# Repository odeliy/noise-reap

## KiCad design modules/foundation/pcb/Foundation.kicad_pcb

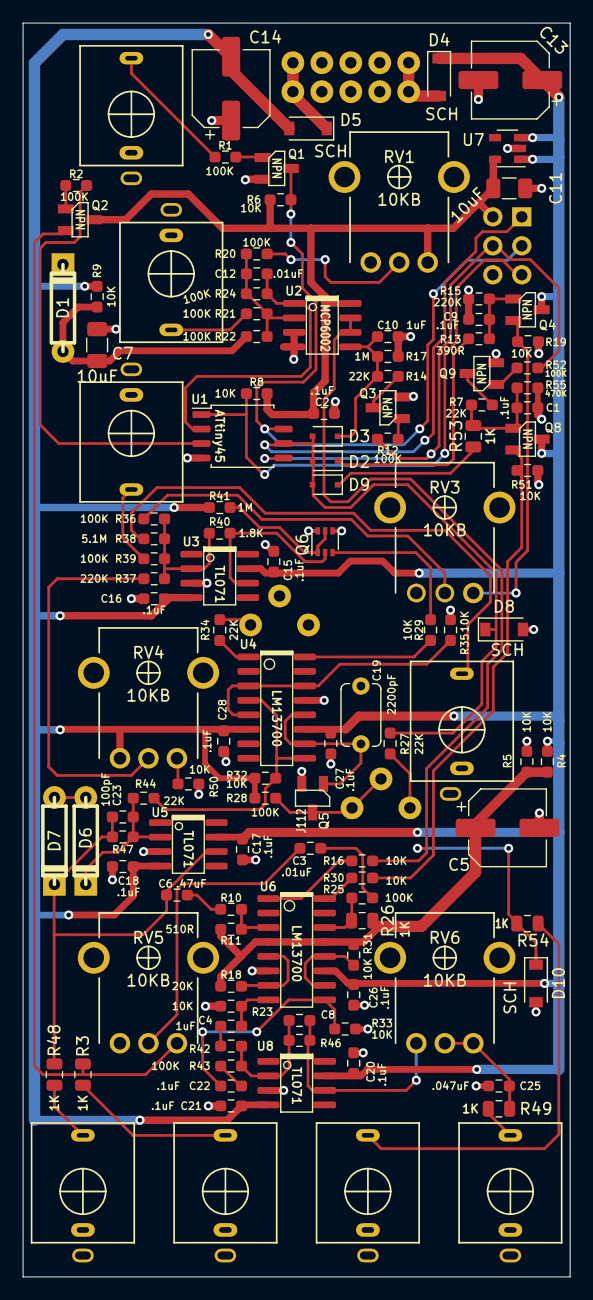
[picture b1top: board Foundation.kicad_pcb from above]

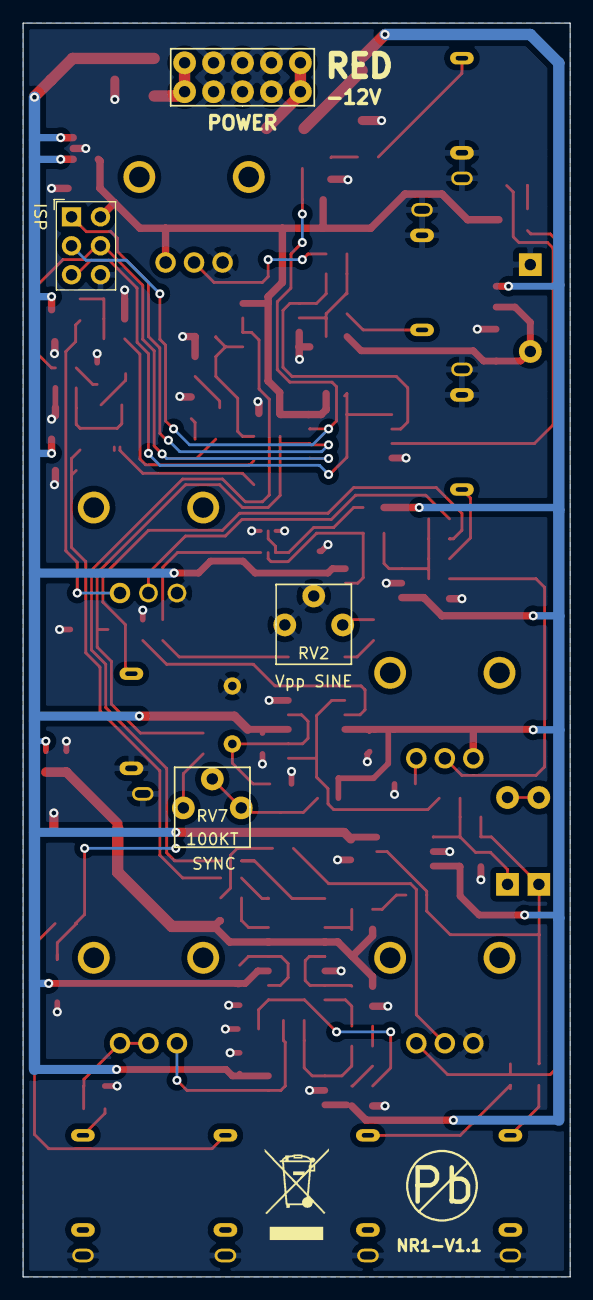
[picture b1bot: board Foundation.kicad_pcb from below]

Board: 2 copper layers, 48.0 x 110.0 mm, 124 parts (4 on the bottom side), 73 nets.

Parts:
C1, C2, C9, C15, C16, C17, C18, C20, C21, C22, C26, C27, C28: .1uF; SM0603
C3, C12: .01uF; SM0603
C4, C10: 1uF; SM0603
C5, C13, C14: 100uF; CP_Elec_6.3x5.4
C6: .47uF; SM0603
C7, C11: 10uF; SM1206
C8, C23: 100pF; SM0603
C19: 2200pF; C_THT_Kemet_Goldmax_C322
C25: .047uF; SM0603
D1, D6, D7: 5.1V; D_THT_DO-41
D2, D3, D9: GEN; D_SOD-323F
D4, D5, D8, D10: SCH; D_SOD-123
J1: STRIKE; AudioJack_QuPing_Pushfit
J2: NOISE; AudioJack_QuPing_Pushfit
J3: AVR-ISP-6; VASCH3x2_ISP
J4: RING_CV; AudioJack_QuPing_Pushfit
J5: POWER; VASCH5x2_unshrouded
J6: NUDGE; AudioJack_QuPing_Pushfit
J7: 1V; AudioJack_QuPing_Pushfit
J8: SINE; AudioJack_QuPing_Pushfit
J9: DRUM; AudioJack_QuPing_Pushfit
J10: ENV_OUT; AudioJack_QuPing_Pushfit
Q1, Q2, Q3, Q4, Q8, Q9: NPN; SOT-23
Q5: J112; SOT-23_nfet
Q6: BC847BPN; SOT-363_SC-70-6
R1, R2, R10, R12, R20, R21, R22, R24, R25, R28, R36, R39, R42, R43, R47, R52: 100K; SM0603
R3, R26, R48, R49, R53, R54: 1K; SM0805
R4, R5, R6, R8, R9, R16, R19, R23, R29, R30, R31, R32, R33, R35, R50, R51: 10K; SM0603
R7, R14, R27, R34, R44: 22K; SM0603
R11: 510R; SM0603
R13: 390R; SM0603
R15, R37, R46: 220K; SM0603
R17, R41: 1M; SM0603
R18: 20K; SM0603
R38: 5.1M; SM0603
R40: 1.8K; SM0603
R55: 470K; SM0603
RV1, RV3, RV4, RV5, RV6: 10KB; POT_9mm_metal
RV2, RV7: 100KT; TRIM_3362P
U1: ATtiny45; SOP-8_5.28x5.23mm_P1.27mm
U2: MCP6002; SOIC-8
U3, U5, U8: TL071; SOIC-8
U4, U6: LM13700; SOIC-16
U7: MIC5205-5.0YM5; SOT-23-5

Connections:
+5V: C2.1, C11.1, J3.2, Q2.C, R6.2, R8.2, RV1.3, U1.8, U2.8, U7.5
+6V: C5.1, R4.2, R5.1, R11.1, R18.2, R26.1, R31.2, U6.4, U6.13
+12V: C13.1, C15.1, C17.1, C20.1, C26.1, C27.1, D4.1, Q4.C, Q8.C, R4.1, U3.7, U4.11, U5.7, U6.11, U7.1, U7.3, U8.7
-5V: C7.1, D1.2, R9.2, R22.2
-12V: C14.2, C16.2, C18.2, C21.2, C28.1, D5.2, R9.1, R28.1, R32.2, R41.2, RV4.1, U3.4, U4.6, U5.4, U8.4
GND: C1.2, C2.2, C5.2, C7.2, C9.2, C10.2, C11.2, C13.2, C14.1, C15.2, C16.1, C17.2, C18.1, C19.2, C20.2, C21.1, C25.2, C26.2, C27.2, C28.2, D1.1, D8.2, D10.2, J1.S, J1.TN, J2.S, J3.6, J4.S, J4.TN, J5.3, J5.4, J5.5, J5.6, J5.7, J5.8, J6.S, J6.TN, J7.S, J7.TN, J8.S, J9.S, J10.S, Q1.E, Q3.E, Q5.S, Q6.4, Q6.6, Q9.E, R5.2, R15.1, R17.2, R19.1, R23.2, R33.2, R35.2, R50.2, R51.2, R55.2, RV1.1, RV2.1, RV2.2, RV3.1, RV5.1, U1.4, U2.3, U2.4, U3.3, U4.13, U5.3, U6.6, U7.2, U8.3
Iexpo: Q6.3, R29.1
unnamed: C1.1, Q8.B, R7.1, R53.1, R55.1
unnamed: C3.1, R25.2
unnamed: C4.2, R23.1, U6.8
unnamed: C6.1, R10.2
unnamed: C8.1, R46.1, RV6.1, U8.6
unnamed: C8.2, R42.1, R43.1, R46.2, U8.2
unnamed: C9.1, Q4.B, R13.1, R15.2
unnamed: C10.1, D3.1, R14.2, R17.1, U2.5
unnamed: C12.2, R20.1, R21.1, R22.1, R24.2, U2.2
unnamed: C19.1, Q5.D, U4.10, U4.12
unnamed: C22.2, R33.1, U6.9
unnamed: C23.2, D6.1, R44.1, R47.2, U5.2
unnamed: C25.1, R49.2, RV6.2, RV6.3
unnamed: D2.1, R13.2
unnamed: D4.2, J5.9, J5.10
unnamed: D5.1, J5.1, J5.2
unnamed: D6.2, D7.2
unnamed: D9.1, R53.2
unnamed: J1.T, R1.2
unnamed: J2.T, R3.1
unnamed: J4.T, R21.2
unnamed: J6.T, R38.2
unnamed: J7.T, R39.2
unnamed: J8.T, R48.1
unnamed: J9.T, R49.1
unnamed: J10.T, R54.1
unnamed: Q1.B, R1.1
unnamed: Q2.B, R2.1
unnamed: Q2.E, R3.2, RV5.3
unnamed: Q3.B, R12.1
unnamed: Q3.C, R14.1
unnamed: Q5.G, R28.2, RV7.2, RV7.3
unnamed: Q6.1, Q6.5, R41.1
unnamed: Q6.2, R40.1, U3.6
unnamed: Q9.B, R52.1
unnamed: Q9.C, R7.2
unnamed: R10.1, R11.2, U6.3
unnamed: R16.2, U6.1
unnamed: R18.1, U6.5, U6.7
unnamed: R20.2, RV1.2
unnamed: R25.1, R26.2, U6.14
unnamed: R27.1, RV7.1
unnamed: R29.2, U4.16
unnamed: R30.2, U6.16
unnamed: R31.1, U6.10, U6.12
unnamed: R34.1, U4.1
unnamed: R34.2, RV2.3
unnamed: R35.1, U4.3, U4.5, U4.14
unnamed: R36.1, R37.1, R38.1, R39.1, R40.2, U3.2
unnamed: R36.2, RV3.2
unnamed: R37.2, RV4.2
unnamed: R50.1, RV4.3
RST: J3.5, R8.1, U1.1
decayPin: C12.1, R24.1, U1.2, U2.1
env1: D10.1, R16.1, R54.2, U2.6, U2.7
env2: Q4.E, R19.2, RV3.3
env3: Q8.E, R30.1, R51.1
noiseDrum: C22.1, R43.2
noisePin: R2.2, U1.3
pulsePin: D2.2, D3.2, D8.1, D9.2, J3.1, R27.2, U1.6
pwmPin: J3.4, R12.2, R52.2, U1.5
sine: C6.2, C23.1, D7.1, R47.1, R48.2, U5.6
sineDrum: C4.1, R42.2
texture: C3.2, RV5.2
triangle: R32.1, R44.2, U4.4, U4.9
trigPin: J3.3, Q1.C, R6.1, U1.7

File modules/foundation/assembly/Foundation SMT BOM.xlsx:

Comment | Designator | Footprint | LCSC Part #
100pF | C8,C23 | C_0603 | C14858
.01uF | C3,C12 | C_0603 | C57112
.047uF | C25 | C_0603 | C1622
.1uF | C28,C27,C26,C9,C1,C15,C2,C16,C17,C18,C20,C21,C22 | C_0603 | C14663
.47uF | C6 | C_0603 | C1623
1uF | C4,C10 | C_0603 | C15849
10uF | C11,C7 | C_1206 | C13585
100uF | C14,C13,C5 | CP_Elec_6.3x5.4 | C134723
390R | R13 | R_0603 | C23151
510R | R11 | R_0603 | C23193
1.8K | R40 | R_0603 | C4177
10K | R33,R19,R51,R50,R30,R4,R5,R6,R8,R9,R16,R23,R29,R31,R32,R35 | R_0603 | C25804
20K | R18 | R_0603 | C4184
22K | R27,R7,R14,R34,R44 | R_0603 | C31850
100K | R52,R2,R1,R10,R12,R20,R21,R22,R24,R25,R28,R36,R39,R42,R43,R47 | R_0603 | C25803
220K | R15,R37,R46 | R_0603 | C22961
470K | R55 | R_0603 | C23178
1M | R17,R41 | R_0603 | C22935
5.1M | R38 | R_0603 | C13320
1K | R54,R53,R48,R26,R3,R49 | R_0805 | C17513
J112 | Q5 | SOT-23-3 | C258195
NPN | Q4,Q9,Q8,Q3,Q2,Q1 | SOT-23-3 | C20526
BC847BPN | Q6 | SOT-363 | C8655
GEN | D9,D3,D2 | D_SOD-323F | C2128
SCH | D10,D8,D5,D4 | D_SOD-123 | C8598
MIC5205-5.0YM5 | U7 | SOT-23-5 | C70431
ATtiny45 | U1 | SOP-8_5.28x5.23mm | C62689
MCP6002 | U2 | SOIC-8 | C7377
TL071 | U5,U8,U3 | SOIC-8 | C107648
LM13700 | U6,U4 | SOIC-16 | C174050

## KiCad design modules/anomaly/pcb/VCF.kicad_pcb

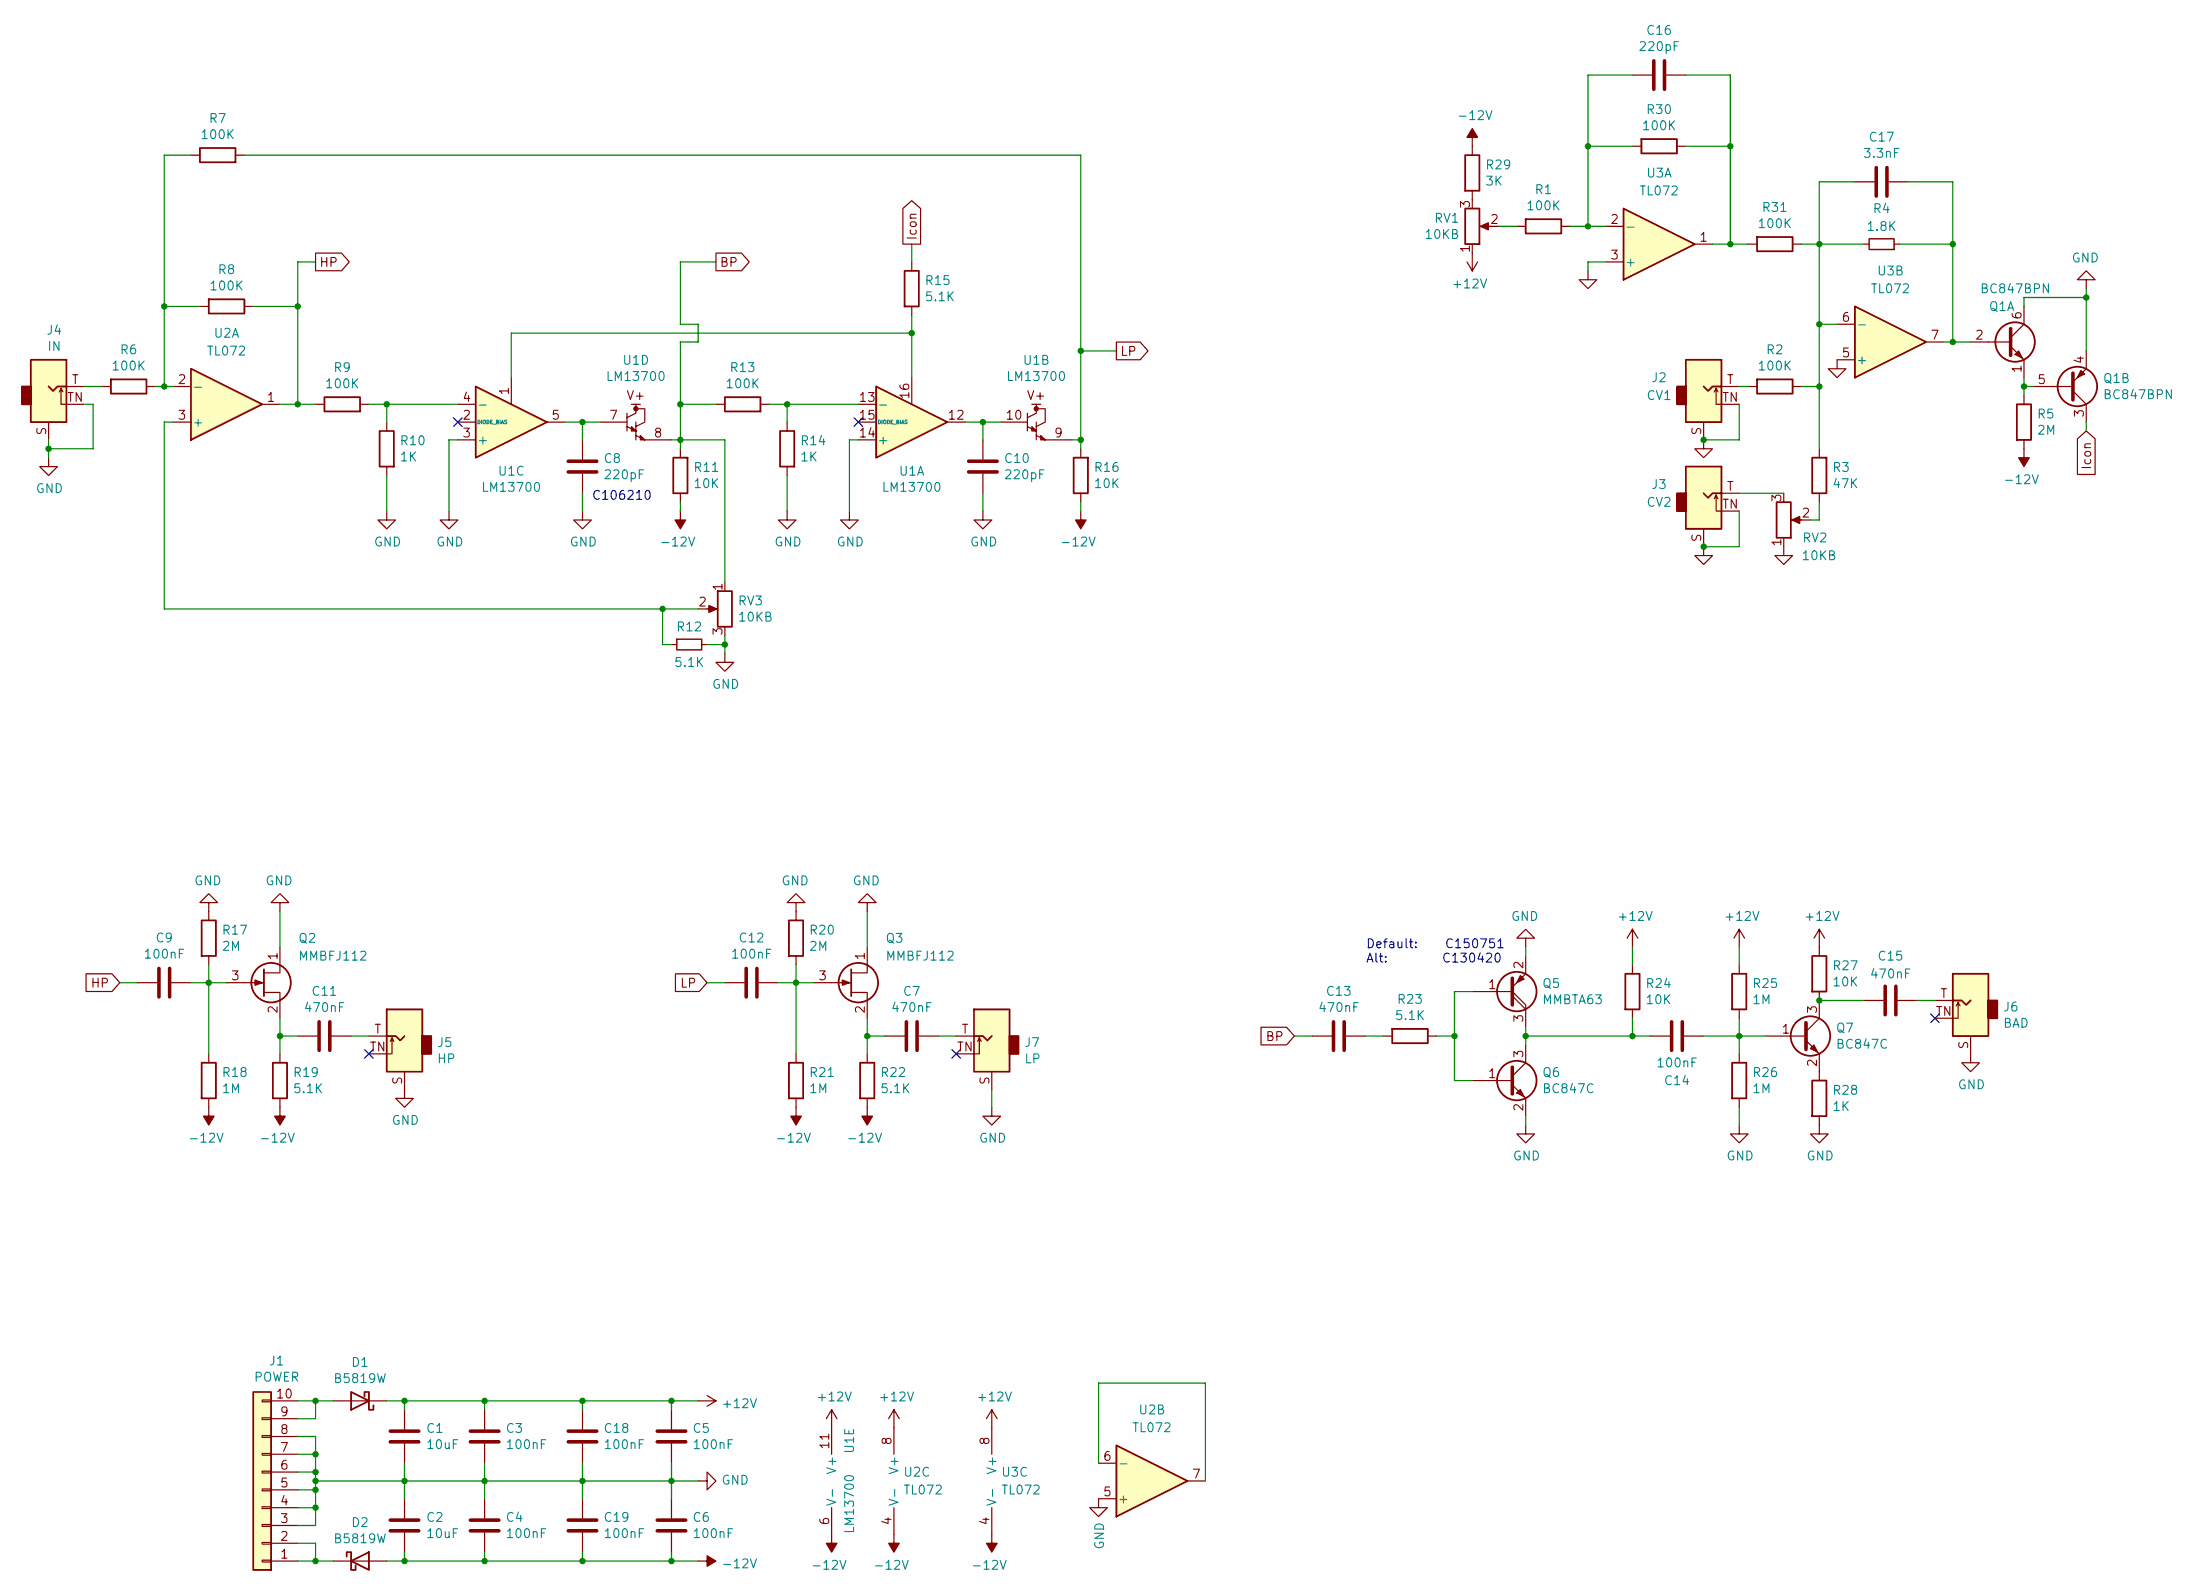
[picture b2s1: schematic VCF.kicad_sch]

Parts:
C1, C2: 10uF; C_1206_3216Metric
C3, C4, C5, C6, C9, C12, C14, C18, C19: 100nF; C_0603_1608Metric
C7, C11, C13, C15: 470nF; C_0805_2012Metric
C8, C10, C16: 220pF; C_0603_1608Metric
C17: 3.3nF; C_0603_1608Metric
D1, D2: B5819W; D_SOD-123
J1: POWER; VASCH5x2_unshrouded
J2: CV1; AudioJack_QuPing_Pushfit
J3: CV2; AudioJack_QuPing_Pushfit
J4: IN; AudioJack_QuPing_Pushfit
J5: HP; AudioJack_QuPing_Pushfit
J6: BAD; AudioJack_QuPing_Pushfit
J7: LP; AudioJack_QuPing_Pushfit
Q1: BC847BPN; SOT-363_SC-70-6
Q2, Q3: MMBFJ112; SOT-23
Q5: MMBTA63; SOT-23
Q6, Q7: BC847C; SOT-23
R1, R2, R6, R7, R8, R9, R13, R30, R31: 100K; R_0603_1608Metric
R3: 47K; R_0603_1608Metric
R4: 1.8K; R_0603_1608Metric
R5, R17, R20: 2M; R_0603_1608Metric
R10, R14, R28: 1K; R_0603_1608Metric
R11, R16, R24, R27: 10K; R_0603_1608Metric
R12, R15, R19, R22, R23: 5.1K; R_0603_1608Metric
R18, R21, R25, R26: 1M; R_0603_1608Metric
R29: 3K; R_0603_1608Metric
RV1, RV2, RV3: 10KB; POT_Bourns_PTV09A-4
U1: LM13700; SOIC-16_3.9x9.9mm_P1.27mm
U2, U3: TL072; SOIC-8_3.9x4.9mm_P1.27mm

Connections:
+12V: C1.1, C3.1, C5.1, C18.1, D1.1 (K), R24.1, R25.1, R27.1, RV1.1, U1.11 (V+), U2.8 (V+), U3.8 (V+)
-12V: C2.2, C4.2, C6.2, C19.2, D2.2 (A), R5.2, R11.1, R16.1, R18.2, R19.2, R21.2, R22.2, R29.1, U1.6 (V-), U2.4 (V-), U3.4 (V-)
BP: C13.2, R11.2, R13.1, RV3.1, U1.8
GND: C1.2, C2.1, C3.2, C4.1, C5.2, C6.1, C8.1, C10.1, C18.2, C19.1, J1.3, J1.4, J1.5, J1.6, J1.7, J1.8, J2.S, J2.TN, J3.S, J3.TN, J4.S, J4.TN, J5.S, J6.S, J7.S, Q1.4 (E2), Q1.6 (C1), Q2.1 (D), Q3.1 (D), Q5.2 (E), Q6.2 (E), R10.2, R12.2, R14.2, R17.1, R20.1, R26.2, R28.2, RV2.1, RV3.3, U1.3 (+), U1.14 (+), U2.5 (+), U3.3 (+), U3.5 (+)
HP: C9.2, R8.1, R9.1, U2.1
Icon: Q1.3 (C2), R15.1
LP: C12.2, R7.2, R16.2, U1.9
unnamed: C7.1, J7.T
unnamed: C7.2, Q3.2 (S), R22.1
unnamed: C8.2, U1.5, U1.7
unnamed: C9.1, Q2.3 (G), R17.2, R18.1
unnamed: C10.2, U1.10, U1.12
unnamed: C11.1, J5.T
unnamed: C11.2, Q2.2 (S), R19.1
unnamed: C12.1, Q3.3 (G), R20.2, R21.1
unnamed: C13.1, R23.2
unnamed: C14.1, Q7.1 (B), R25.2, R26.1
unnamed: C14.2, Q5.3 (C), Q6.3 (C), R24.2
unnamed: C15.1, J6.T
unnamed: C15.2, Q7.3 (C), R27.2
unnamed: C16.1, R30.1, R31.2, U3.1
unnamed: C16.2, R1.1, R30.2, U3.2 (-)
unnamed: C17.1, Q1.2 (B1), R4.1, U3.7
unnamed: C17.2, R2.1, R3.2, R4.2, R31.1, U3.6 (-)
unnamed: D1.2 (A), J1.9, J1.10
unnamed: D2.1 (K), J1.1, J1.2
unnamed: J2.T, R2.2
unnamed: J3.T, RV2.3
unnamed: J4.T, R6.2
unnamed: Q1.1 (E1), Q1.5 (B2), R5.1
unnamed: Q5.1 (B), Q6.1 (B), R23.1
unnamed: Q7.2 (E), R28.1
unnamed: R1.2, RV1.2
unnamed: R3.1, RV2.2
unnamed: R6.1, R7.1, R8.2, U2.2 (-)
unnamed: R9.2, R10.1, U1.4 (-)
unnamed: R12.1, RV3.2, U2.3 (+)
unnamed: R13.2, R14.1, U1.13 (-)
unnamed: R15.2, U1.1, U1.16
unnamed: R29.2, RV1.3
unnamed: U2.6 (-), U2.7

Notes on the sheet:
C106210
Default: C150751 Alt: C130420

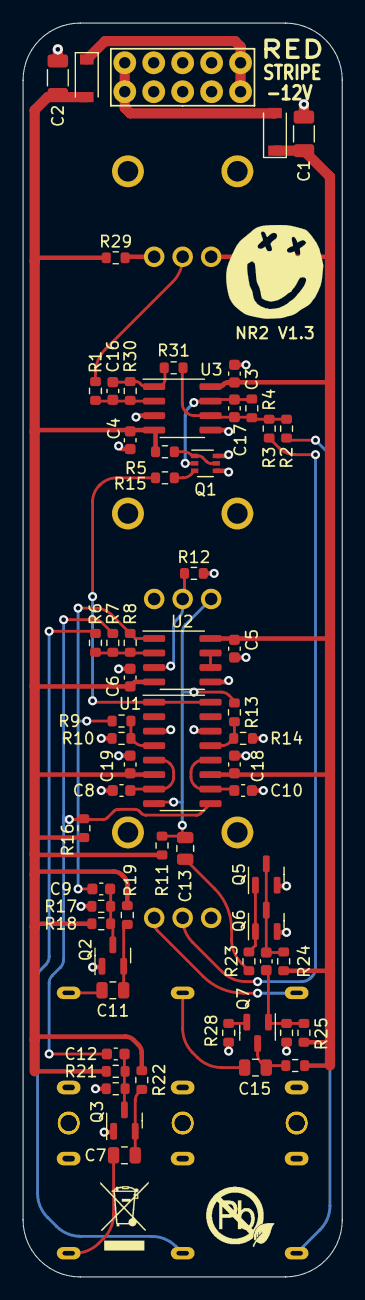
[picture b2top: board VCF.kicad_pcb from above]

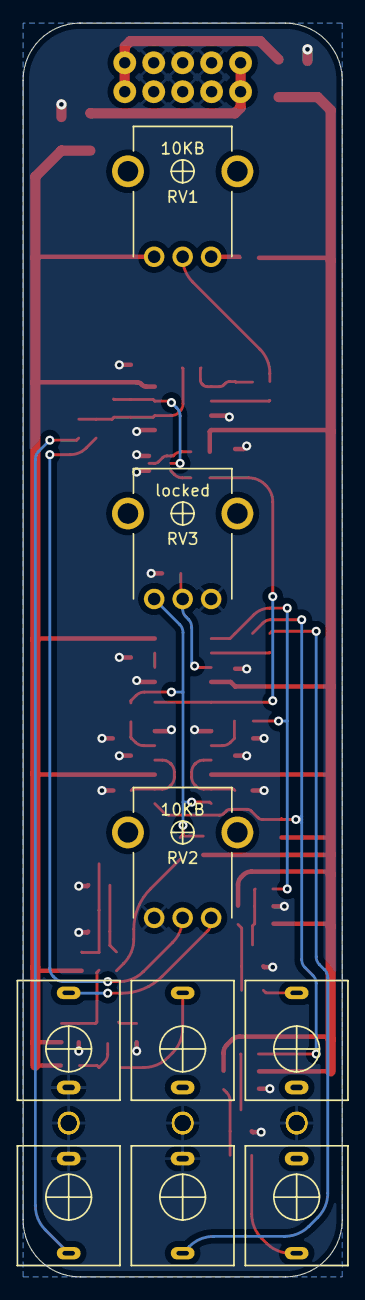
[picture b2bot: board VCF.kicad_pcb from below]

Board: 2 copper layers, 28.0 x 110.0 mm, 72 parts (9 on the bottom side), 41 nets.

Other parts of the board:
U$3: Val**; PB_FREE_EAGLE

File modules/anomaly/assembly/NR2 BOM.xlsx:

Comment | Designator | Footprint | LCSC Part #
220pF NP0 | C16,C10,C8 | C_0603_1608Metric | C106210
3.3nF | C17 | C_0603_1608Metric | C1613
100nF | C14,C3,C12,C9,C6,C4,C19,C18,C5 | C_0603_1608Metric | C14663
470nF | C11,C15,C13,C7 | C_0805_2012Metric | C13967
10uF | C1,C2 | C_1206_3216Metric | C13585
B5819W | D1,D2 | D_SOD-123 | C8598
BC847C | Q6,Q7 | SOT-23 | C181141
MMBTA63-7-F | Q5 | SOT-23 | C130420
MMBFJ112 | Q3,Q2 | SOT-23 | C258195
BC847BPN | Q1 | SOT-363_SC-70-6 | C8655
1K | R10,R14,R28 | R_0603_1608Metric | C21190
1.8K | R4 | R_0603_1608Metric | C4177
3K | R29 | R_0603_1608Metric | C4211
5.1K | R12,R23,R22,R15,R19 | R_0603_1608Metric | C23186
10K | R27,R11,R24,R16 | R_0603_1608Metric | C25804
47K | R3 | R_0603_1608Metric | C25819
100K | R30,R2,R7,R31,R6,R8,R13,R1,R9 | R_0603_1608Metric | C25803
2M | R17,R5,R20 | R_0603_1608Metric | C22976
1M | R25,R18,R21,R26 | R_0603_1608Metric | C22935
LM13700 | U1 | SOIC-16_3.9x9.9mm_P1.27mm | C174050
TL072 | U2,U3 | SOIC-8_3.9x4.9mm_P1.27mm | C6961

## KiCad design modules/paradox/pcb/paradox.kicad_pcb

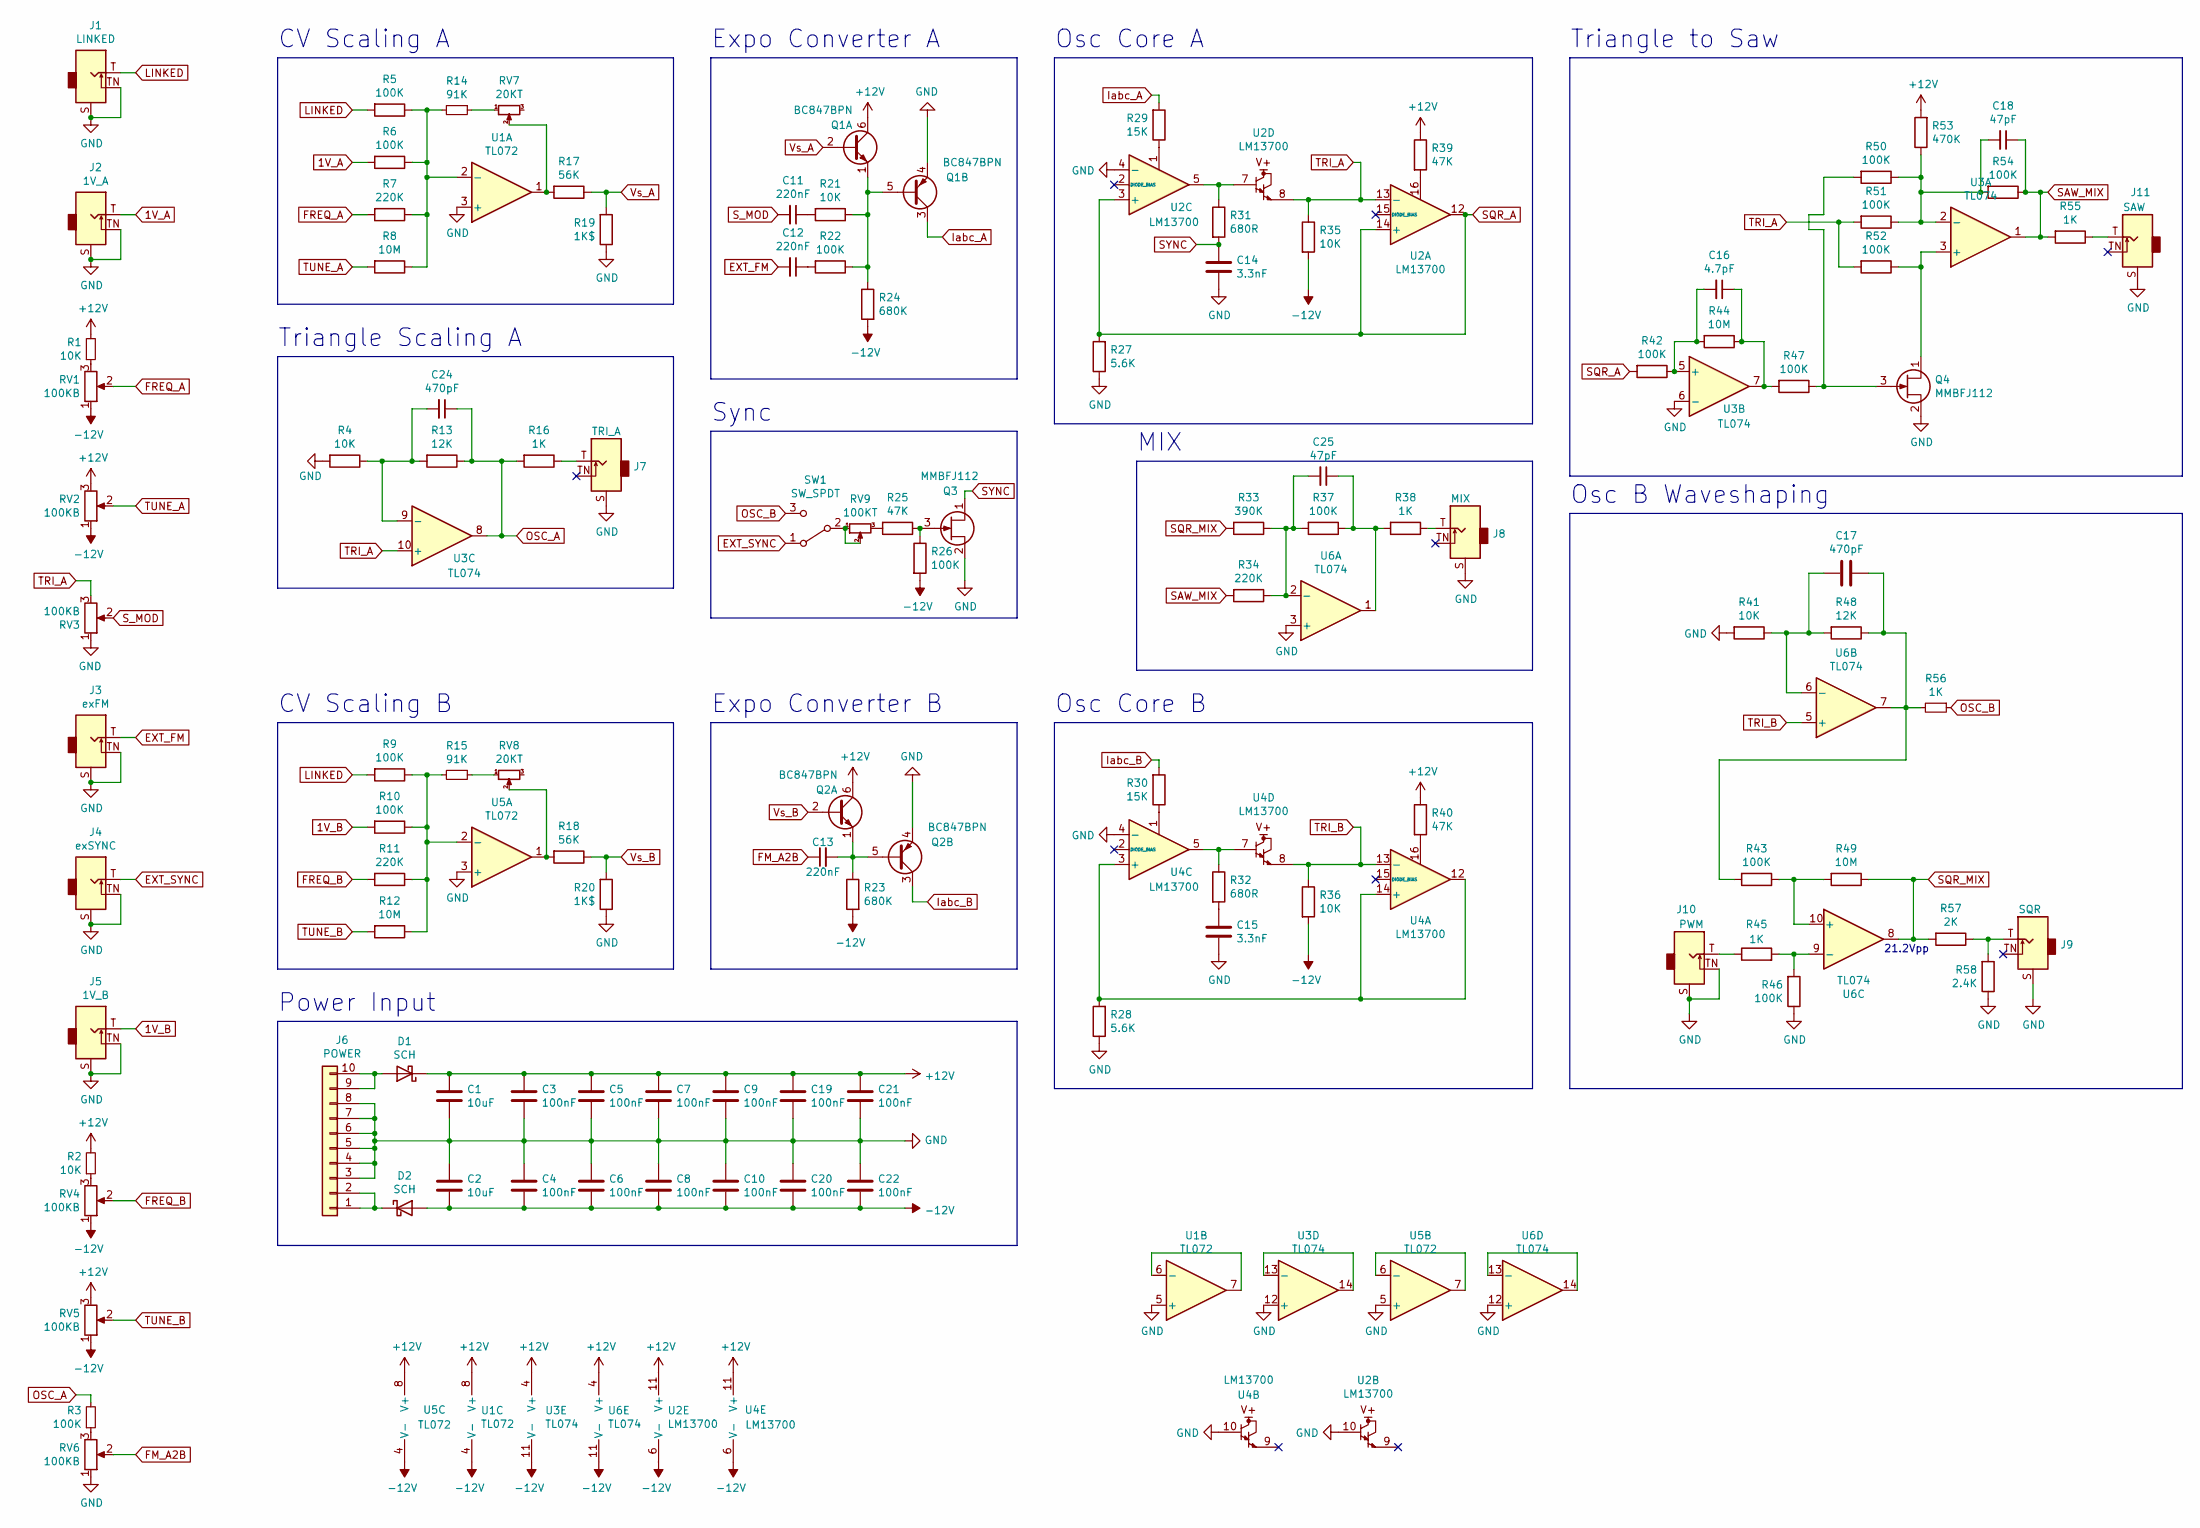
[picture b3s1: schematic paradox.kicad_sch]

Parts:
C1, C2: 10uF; C_1206_3216Metric; JLC C72477
C3, C4, C5, C6, C7, C8, C9, C10, C19, C20, C21, C22: 100nF; C_0402_1005Metric
C11, C12, C13: 220nF; C_0603_1608Metric
C14, C15: 3.3nF; C_0603_1608Metric
C16: 4.7pF; C_0603_1608Metric
C17, C24: 470pF; C_0603_1608Metric
C18, C25: 47pF; C_0603_1608Metric
D1, D2: SCH; D_SOD-123
J1: LINKED; AudioJack_QuPing_Pushfit
J2: 1V_A; AudioJack_QuPing_Pushfit
J3: exFM; AudioJack_QuPing_Pushfit
J4: exSYNC; AudioJack_QuPing_Pushfit
J5: 1V_B; AudioJack_QuPing_Pushfit
J6: POWER; VASCH5x2_unshrouded
J7: TRI_A; AudioJack_QuPing_Pushfit
J8: MIX; AudioJack_QuPing_Pushfit
J9: SQR; AudioJack_QuPing_Pushfit
J10: PWM; AudioJack_QuPing_Pushfit
J11: SAW; AudioJack_QuPing_Pushfit
Q1, Q2: BC847BPN; SOT-363_SC-70-6
Q3, Q4: MMBFJ112; SOT-23
R1, R2, R4, R21, R35, R36, R41: 10K; R_0603_1608Metric
R3, R5, R6, R9, R10, R22, R26, R37, R42, R43, R46, R47, R50, R51, R52, R54: 100K; R_0603_1608Metric
R7, R11, R34: 220K; R_0603_1608Metric
R8, R12, R44, R49: 10M; R_0603_1608Metric
R13, R48: 12K; R_0603_1608Metric
R14, R15: 91K; R_0603_1608Metric
R16, R38, R55: 1K; R_1206_3216Metric
R17, R18: 56K; R_0603_1608Metric
R19, R20: 1K$; R_THT_Tempco
R23, R24: 680K; R_0603_1608Metric
R25, R39, R40: 47K; R_0603_1608Metric
R27, R28: 5.6K; R_0603_1608Metric
R29, R30: 15K; R_0603_1608Metric
R31, R32: 680R; R_0603_1608Metric
R33: 390K; R_0603_1608Metric
R45, R56: 1K; R_0603_1608Metric
R53: 470K; R_0603_1608Metric
R57: 2K; R_0603_1608Metric
R58: 2.4K; R_0603_1608Metric
RV1, RV3, RV4, RV6: 100KB; POT_9mm_P0915N
RV2, RV5: 100KB; POT_9mm_Tall-Trimmer
RV7, RV8: 20KT; TRIM_3296W
RV9: 100KT; TRIM_3296W
SW1: SW_SPDT; SW_SPDT_1M-Series_PC-Thru-Hole
U1, U5: TL072; SOIC-8_3.9x4.9mm_P1.27mm
U2, U4: LM13700; SOIC-16_3.9x9.9mm_P1.27mm
U3, U6: TL074; TSSOP-14_4.4x5mm_P0.65mm

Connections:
1V_A: J2.T, R6.2
1V_B: J5.T, R10.2
+12V: C1.1, C3.1, C5.1, C7.1, C9.1, C19.1, C21.1, D1.1 (K), Q1.6 (C1), Q2.6 (C1), R1.2, R2.2, R39.1, R40.1, R53.2, RV2.3, RV5.3, U1.8 (V+), U2.11 (V+), U3.4 (V+), U4.11 (V+), U5.8 (V+), U6.4 (V+)
-12V: C2.2, C4.2, C6.2, C8.2, C10.2, C20.2, C22.2, D2.2 (A), R23.2, R24.2, R26.2, R35.2, R36.2, RV1.1, RV2.1, RV4.1, RV5.1, U1.4 (V-), U2.6 (V-), U3.11 (V-), U4.6 (V-), U5.4 (V-), U6.11 (V-)
EXT_FM: C12.2, J3.T
EXT_SYNC: J4.T, SW1.1 (A)
FM_A2B: C13.1, RV6.2
FREQ_A: R7.2, RV1.2
FREQ_B: R11.2, RV4.2
GND: C1.2, C2.1, C3.2, C4.1, C5.2, C6.1, C7.2, C8.1, C9.2, C10.1, C14.2, C15.2, C19.2, C20.1, C21.2, C22.1, J1.S, J1.TN, J2.S, J2.TN, J3.S, J3.TN, J4.S, J4.TN, J5.S, J5.TN, J6.3, J6.4, J6.5, J6.6, J6.7, J6.8, J7.S, J8.S, J9.S, J10.S, J10.TN, J11.S, Q1.4 (E2), Q2.4 (E2), Q3.2 (S), Q4.2 (S), R4.2, R19.1, R20.1, R27.1, R28.1, R41.2, R46.1, R58.1, RV3.1, RV6.1, U1.3 (+), U1.5 (+), U2.4 (-), U2.10, U3.6 (-), U3.12 (+), U4.4 (-), U4.10, U5.3 (+), U5.5 (+), U6.3 (+), U6.12 (+)
Iabc_A: Q1.3 (C2), R29.2
Iabc_B: Q2.3 (C2), R30.2
LINKED: J1.T, R5.2, R9.2
unnamed: C11.1, R21.2
unnamed: C12.1, R22.2
unnamed: C13.2, Q2.1 (E1), Q2.5 (B2), R23.1
unnamed: C15.1, R32.2
unnamed: C16.1, R44.1, R47.2, U3.7
unnamed: C16.2, R42.1, R44.2, U3.5 (+)
unnamed: C17.1, R43.2, R48.1, R56.2, U6.7
unnamed: C17.2, R41.1, R48.2, U6.6 (-)
unnamed: C18.2, R50.1, R51.1, R53.1, R54.2, U3.2 (-)
unnamed: C24.2, R4.1, R13.2, U3.9 (-)
unnamed: C25.1, R37.1, R38.2, U6.1
unnamed: C25.2, R33.1, R34.1, R37.2, U6.2 (-)
unnamed: D1.2 (A), J6.9, J6.10
unnamed: D2.1 (K), J6.1, J6.2
unnamed: J7.T, R16.1
unnamed: J8.T, R38.1
unnamed: J9.T, R57.1, R58.2
unnamed: J10.T, R45.1
unnamed: J11.T, R55.1
unnamed: Q1.1 (E1), Q1.5 (B2), R21.1, R22.1, R24.1
unnamed: Q3.3 (G), R25.1, R26.1
unnamed: Q4.1 (D), R52.1, U3.3 (+)
unnamed: Q4.3 (G), R47.1, R50.2
unnamed: R1.1, RV1.3
unnamed: R2.1, RV4.3
unnamed: R3.1, RV6.3
unnamed: R9.1, R10.1, R11.1, R12.1, R15.2, U5.2 (-)
unnamed: R14.1, RV7.1
unnamed: R5.1, R6.1, R7.1, R8.1, R14.2, U1.2 (-)
unnamed: R15.1, RV8.1
unnamed: R17.2, RV7.2, U1.1
unnamed: R18.2, RV8.2, U5.1
unnamed: R25.2, RV9.3
unnamed: R28.2, U4.3 (+), U4.12, U4.14 (+)
unnamed: R29.1, U2.1
unnamed: R30.1, U4.1
unnamed: R31.1, U2.5, U2.7
unnamed: R32.1, U4.5, U4.7
unnamed: R39.2, U2.16
unnamed: R40.2, U4.16
unnamed: R43.1, R49.2, U6.10 (+)
unnamed: R45.2, R46.2, U6.9 (-)
unnamed: RV9.1, RV9.2, SW1.2 (B)
unnamed: U1.6 (-), U1.7
unnamed: U3.13 (-), U3.14
unnamed: U5.6 (-), U5.7
unnamed: U6.13 (-), U6.14
OSC_A: C24.1, R3.2, R13.1, R16.2, U3.8
OSC_B: R56.1, SW1.3 (C)
SAW_MIX: C18.1, R34.2, R54.1, R55.2, U3.1
SQR_A: R27.2, R42.2, U2.3 (+), U2.12, U2.14 (+)
SQR_MIX: R33.2, R49.1, R57.2, U6.8
SYNC: C14.1, Q3.1 (D), R31.2
S_MOD: C11.2, RV3.2
TRI_A: R35.1, R51.2, R52.2, RV3.3, U2.8, U2.13 (-), U3.10 (+)
TRI_B: R36.1, U4.8, U4.13 (-), U6.5 (+)
TUNE_A: R8.2, RV2.2
TUNE_B: R12.2, RV5.2
Vs_A: Q1.2 (B1), R17.1, R19.2
Vs_B: Q2.2 (B1), R18.1, R20.2

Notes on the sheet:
Sync
MIX
21.2Vpp
Expo Converter B
Osc Core A
CV Scaling A
Osc B Waveshaping
Power Input
Osc Core B
Expo Converter A
CV Scaling B
Triangle to Saw
Triangle Scaling A

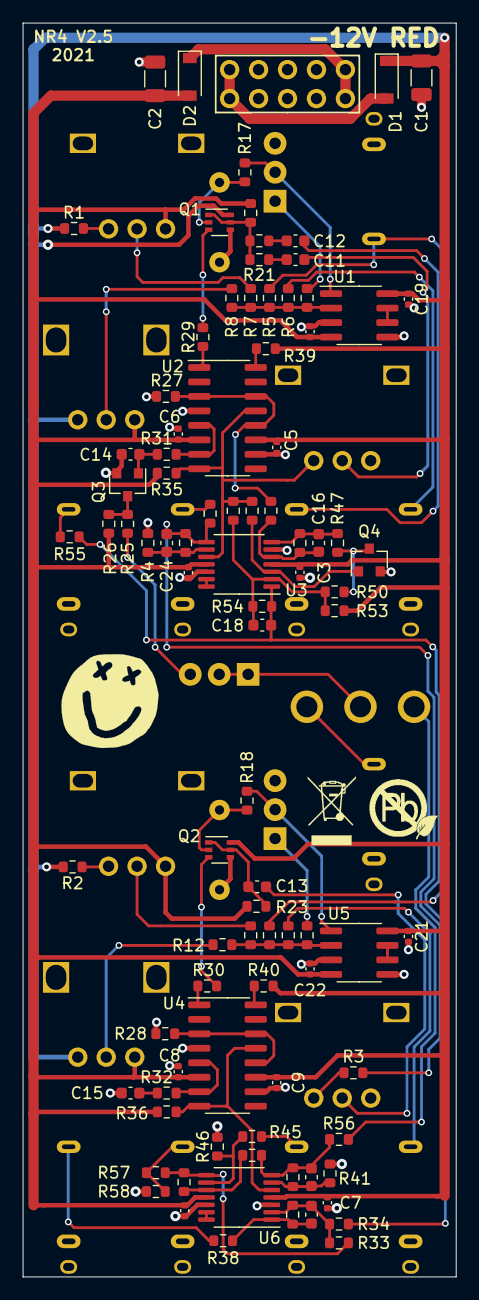
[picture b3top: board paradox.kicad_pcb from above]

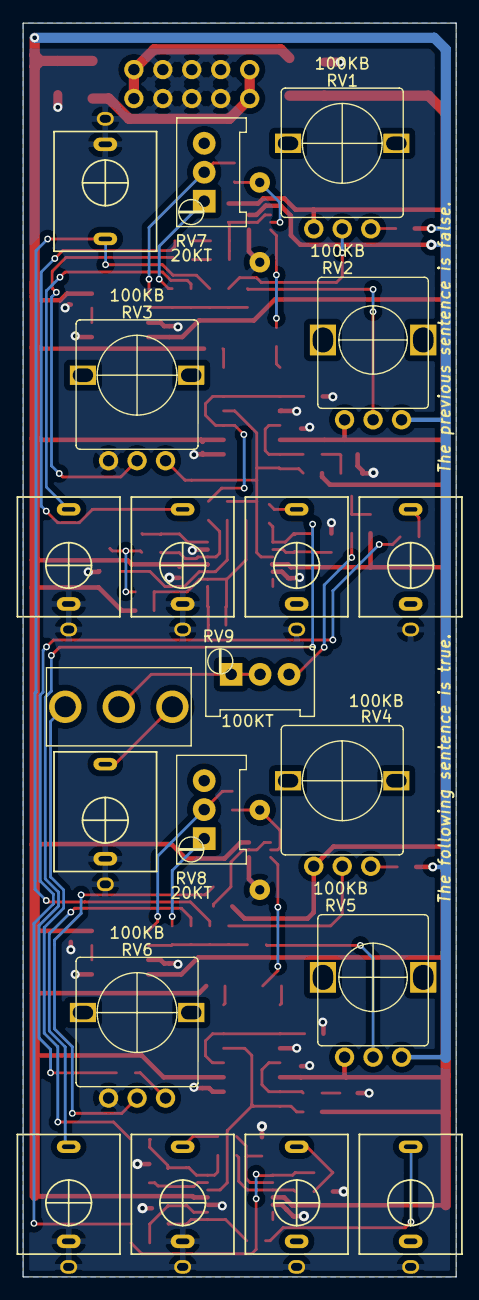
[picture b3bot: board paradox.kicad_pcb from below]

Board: 2 copper layers, 38.0 x 110.0 mm, 116 parts (20 on the bottom side), 73 nets.

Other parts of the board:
U$3: Val**; ROHS_LOGO

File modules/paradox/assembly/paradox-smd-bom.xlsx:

Comment | Designator | Footprint | LCSC Part #
2.4K | R58 | R_0603_1608Metric | C22940
2K | R57 | R_0603_1608Metric | C22975
1K | R56,R45,R55,R38,R16 | R_0603_1608Metric | C21190
10M | R49,R44,R12,R8 | R_0603_1608Metric | C7250
12K | R48,R13 | R_0603_1608Metric | C22790
100K | R46,R43,R54,R52,R51,R50,R47,R42,R37,R26,R22,R10,R9,R6,R5,R3 | R_0603_1608Metric | C25803
10K | R41,R36,R35,R21,R4,R2,R1 | R_0603_1608Metric | C25804
470pF | C17,C24 | C_0603_1608Metric | C1620
47pF | C25,C18 | C_0603_1608Metric | C1671
TL074CPWR | U6,U3 | TSSOP-14_4.4x5mm_P0.65mm | C96507
TL072CDT | U5,U1 | SOIC-8_3.9x4.9mm_P1.27mm | C6961
100nF | C22,C21,C20,C19,C10,C9,C8,C7,C6,C5,C4,C3 | C_0402_1005Metric | C1525
680R | R31,R32 | R_0603_1608Metric | C23228
10uF | C2,C1 | C_1206_3216Metric | C13585
LM13700 | U4,U2 | SOIC-16_3.9x9.9mm_P1.27mm | C174050
470K | R53 | R_0603_1608Metric | C23178
47K | R40,R39,R25 | R_0603_1608Metric | C25819
220K | R34,R11,R7 | R_0603_1608Metric | C22961
390K | R33 | R_0603_1608Metric | C23150
15K | R30,R29 | R_0603_1608Metric | C22809
5.6K | R28,R27 | R_0603_1608Metric | C23189
680K | R24,R23 | R_0603_1608Metric | C25822
56K | R18,R17 | R_0603_1608Metric | C23206
91K | R15,R14 | R_0603_1608Metric | C23265
MMBFJ112 | Q4,Q3 | SOT-23 | C258195
BC847BPN | Q2,Q1 | SOT-363_SC-70-6 | C8655
B5819W | D2,D1 | D_SOD-123 | C8598
4.7pF | C16 | C_0603_1608Metric | C1669
3.3nF | C15,C14 | C_0603_1608Metric | C55395
220nF | C13,C12,C11 | C_0603_1608Metric | C21120

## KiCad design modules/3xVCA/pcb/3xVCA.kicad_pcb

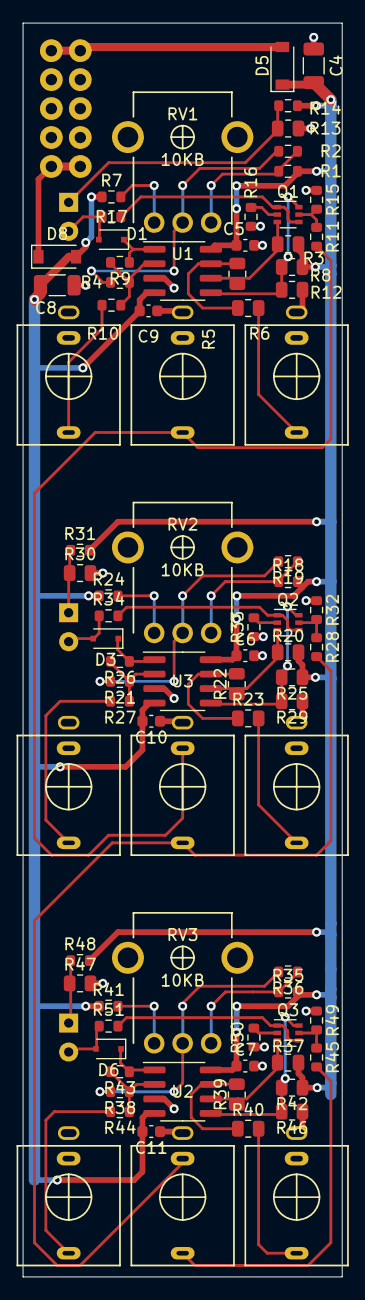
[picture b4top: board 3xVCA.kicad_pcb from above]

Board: 2 copper layers, 28.0 x 110.0 mm, 86 parts (1 on the bottom side), 53 nets.

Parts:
C4, C8: 10uF; C_1206_3216Metric
C5, C6, C7, C9, C10, C11: .1uF; C_0603_1608Metric
D1, D3, D6: 1N4148WS; D_SOD-323F
D2, D4, D7: LED; LED_3mm
D5, D8: B5819W; D_SOD-123
J1: OUT1; AudioJack_QuPing_Pushfit
J2: CV1; AudioJack_QuPing_Pushfit
J3: IN1; AudioJack_QuPing_Pushfit
J4: OUT2; AudioJack_QuPing_Pushfit
J5: CV2; AudioJack_QuPing_Pushfit
J6: IN2; AudioJack_QuPing_Pushfit
J7: OUT3; AudioJack_QuPing_Pushfit
J8: POWER; VASCH5x2_unshrouded
J9: CV3; AudioJack_QuPing_Pushfit
J10: IN3; AudioJack_QuPing_Pushfit
Q1, Q2, Q3: BC847S; SOT-363_SC-70-6
R1, R2, R18, R19, R35, R36: 3.9K; R_0603_1608Metric
R3, R8, R20, R25, R37, R42: 12K$; R_0805_2012Metric
R4, R9, R10, R11, R21, R26, R27, R28, R38, R43, R44, R45: 100K; R_0603_1608Metric
R5, R12, R22, R29, R39, R46: 33K$; R_0805_2012Metric
R6, R13, R23, R30, R40, R47: 1K; R_0805_2012Metric
R7, R15, R16, R24, R32, R33, R41, R49, R50: 510R; R_0603_1608Metric
R14, R17, R31, R34, R48, R51: 12K; R_0603_1608Metric
RV1, RV2, RV3: 10KB; POT_9mm_metal
U1, U2, U3: TL072CDT; SOIC-8_3.9x4.9mm_P1.27mm

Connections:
+12V: C4.1, C5.1, C6.1, C7.1, D5.1, R1.2, R3.2, R8.1, R14.2, R18.2, R20.2, R25.1, R31.2, R35.2, R37.2, R42.1, R48.2, U1.8, U2.8, U3.8
-12V: C8.2, C9.2, C10.2, C11.2, D8.2, R7.1, R24.1, R41.1, U1.4, U2.4, U3.4
GND: C4.2, C5.2, C6.2, C7.2, C8.1, C9.1, C10.1, C11.1, J1.S, J2.S, J3.S, J4.S, J5.S, J6.S, J7.S, J8.3, J8.4, J8.5, J8.6, J8.7, J8.8, J9.S, J10.S, R12.1, R13.2, R15.1, R16.1, R29.1, R30.2, R32.1, R33.1, R46.1, R47.2, R49.1, R50.1, U1.3, U2.3, U3.3
unnamed: D1.1, R9.1, U1.1
unnamed: D1.2, D2.1, R17.1
unnamed: D2.2, R13.1, R14.1
unnamed: D3.1, R26.1, U3.1
unnamed: D3.2, D4.1, R34.1
unnamed: D4.2, R30.1, R31.1
unnamed: D5.2, J8.9, J8.10
unnamed: D6.1, R43.1, U2.1
unnamed: D6.2, D7.1, R51.1
unnamed: D7.2, R47.1, R48.1
unnamed: D8.1, J8.1, J8.2
unnamed: J1.T, R6.2
unnamed: J2.T, R10.2
unnamed: J3.T, J6.TN, R11.2
unnamed: J4.T, R23.2
unnamed: J5.T, R27.2
unnamed: J7.T, R40.2
unnamed: J9.T, R44.2
unnamed: J10.T, R45.2
unnamed: J6.T, J10.TN, R28.2
unnamed: Q1.1, Q1.4, R17.2
unnamed: Q1.2, R16.2
unnamed: Q1.3, R3.1, R5.1, U1.6
unnamed: Q1.5, R11.1, R15.2
unnamed: Q1.6, R8.2, R12.2, U1.5
unnamed: Q2.1, Q2.4, R34.2
unnamed: Q2.2, R33.2
unnamed: Q2.3, R20.1, R22.1, U3.6
unnamed: Q2.5, R28.1, R32.2
unnamed: Q2.6, R25.2, R29.2, U3.5
unnamed: Q3.1, Q3.4, R51.2
unnamed: Q3.2, R50.2
unnamed: Q3.3, R37.1, R39.1, U2.6
unnamed: Q3.5, R45.1, R49.2
unnamed: Q3.6, R42.2, R46.2, U2.5
unnamed: R1.1, R2.1, RV1.3
unnamed: R2.2, R4.2, RV1.2
unnamed: R5.2, R6.1, U1.7
unnamed: R7.2, RV1.1
unnamed: R4.1, R9.2, R10.1, U1.2
unnamed: R18.1, R19.1, RV2.3
unnamed: R19.2, R21.2, RV2.2
unnamed: R21.1, R26.2, R27.1, U3.2
unnamed: R22.2, R23.1, U3.7
unnamed: R24.2, RV2.1
unnamed: R35.1, R36.1, RV3.3
unnamed: R36.2, R38.2, RV3.2
unnamed: R38.1, R43.2, R44.1, U2.2
unnamed: R39.2, R40.1, U2.7
unnamed: R41.2, RV3.1

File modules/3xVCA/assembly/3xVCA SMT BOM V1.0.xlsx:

Comment | Designator | Footprint | LCSC Part #
10uF | C8,C4 | C_1206 | C13585
0.1uF | C11,C10,C9,C7,C6,C5 | C_0603 | C14663
510R | R41,R24,R7,R50,R49,R33,R32,R16,R15 | R_0603 | C23193
3.9K | R35,R36,R19,R18,R2,R1 | R_0603 | C23018
12K | R51,R48,R34,R31,R17,R14 | R_0603 | C22790
100K | R45,R44,R43,R38,R28,R27,R26,R21,R11,R10,R9,R4 | R_0603 | C25803
1K | R47,R40,R30,R23,R13,R6 | R_0805 | C17513
12K (0.1%) | R42,R37,R25,R20,R8,R3 | R_0805 | C97163
33K (0.1%) | R46,R39,R29,R22,R12,R5 | R_0805 | C59057
BC847S | Q3,Q2,Q1 | SOT-363 | C148112
1N4148WS | D6,D3,D1 | D_SOD-323-F | C2128
B5819W | D8,D5 | D_SOD-123 | C8598
TL072CDT | U3,U2,U1 | SOIC-8_3.9x4.9mm_P1.27mm | C6961
